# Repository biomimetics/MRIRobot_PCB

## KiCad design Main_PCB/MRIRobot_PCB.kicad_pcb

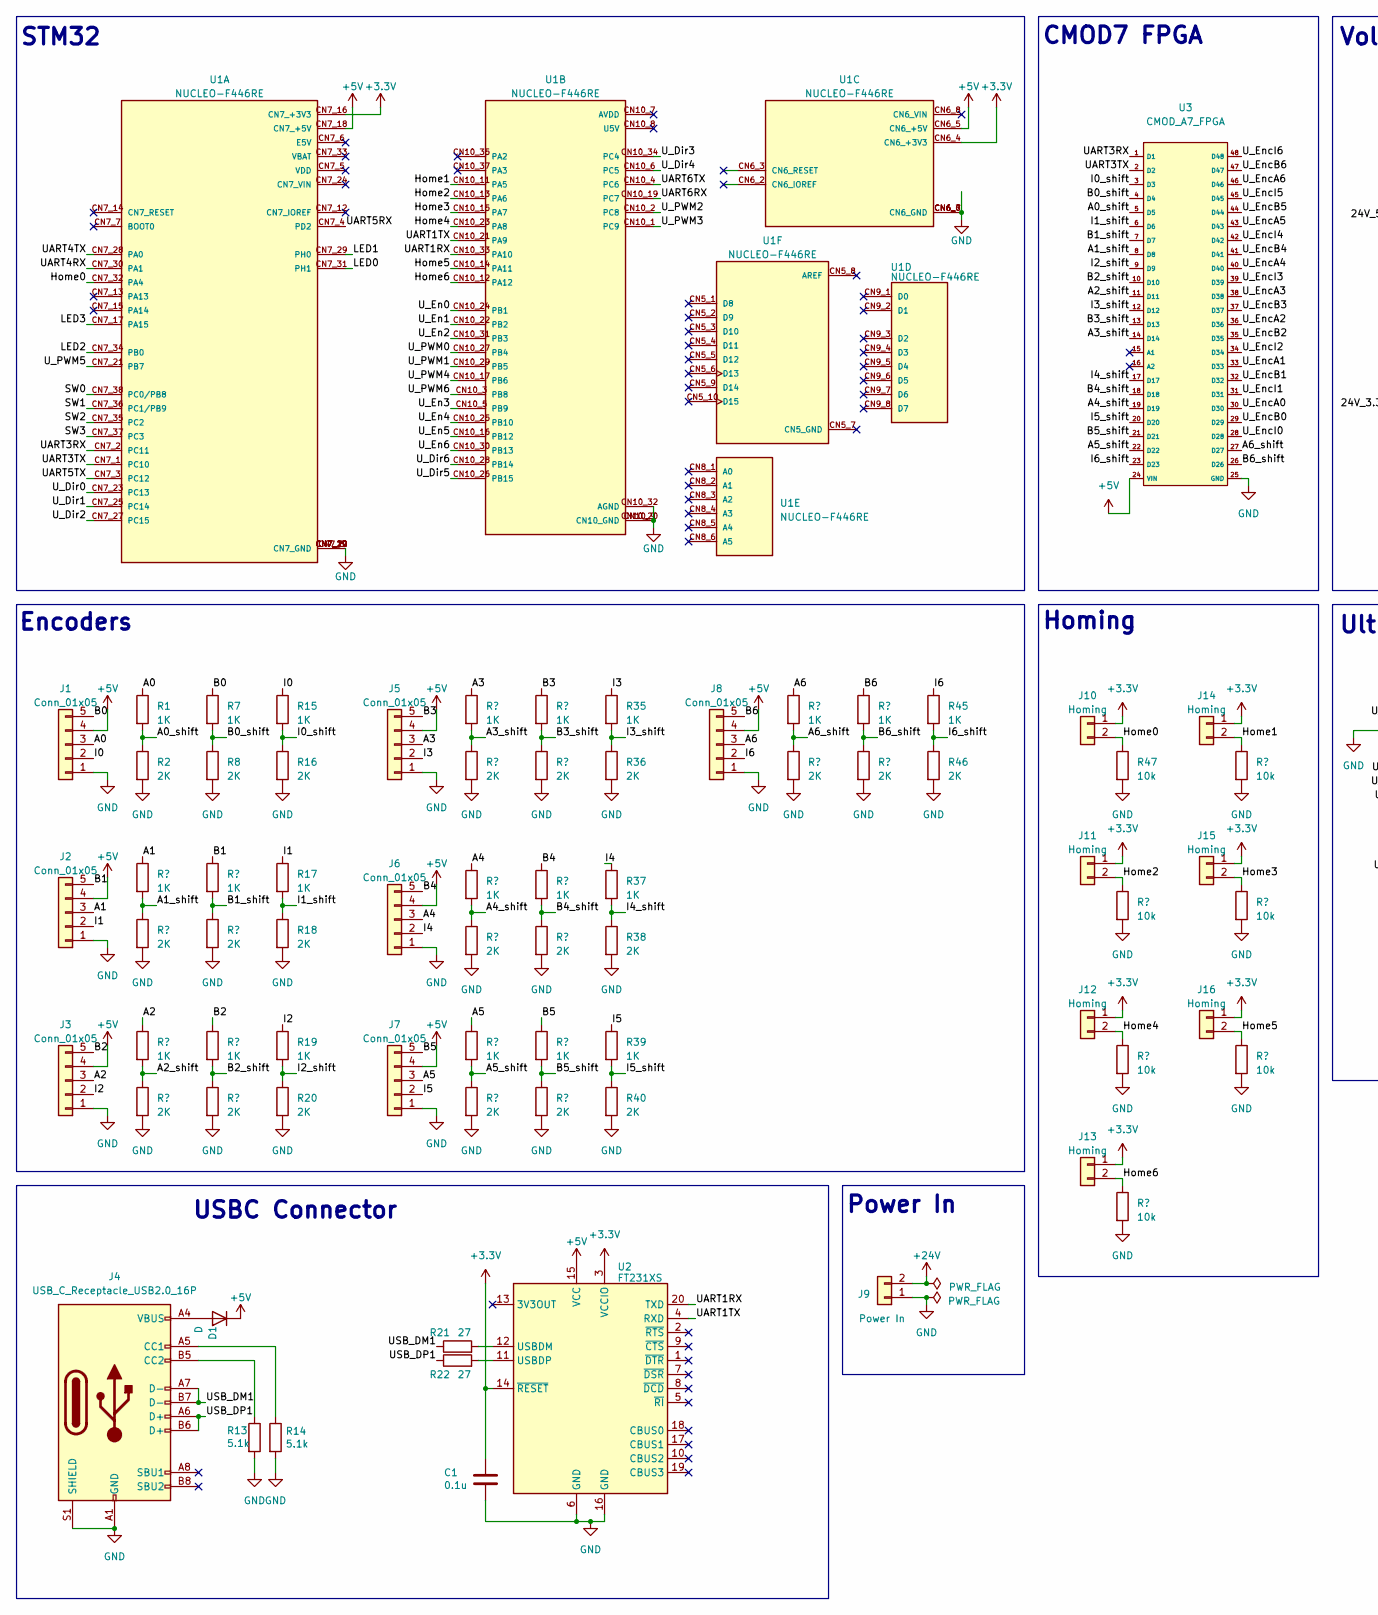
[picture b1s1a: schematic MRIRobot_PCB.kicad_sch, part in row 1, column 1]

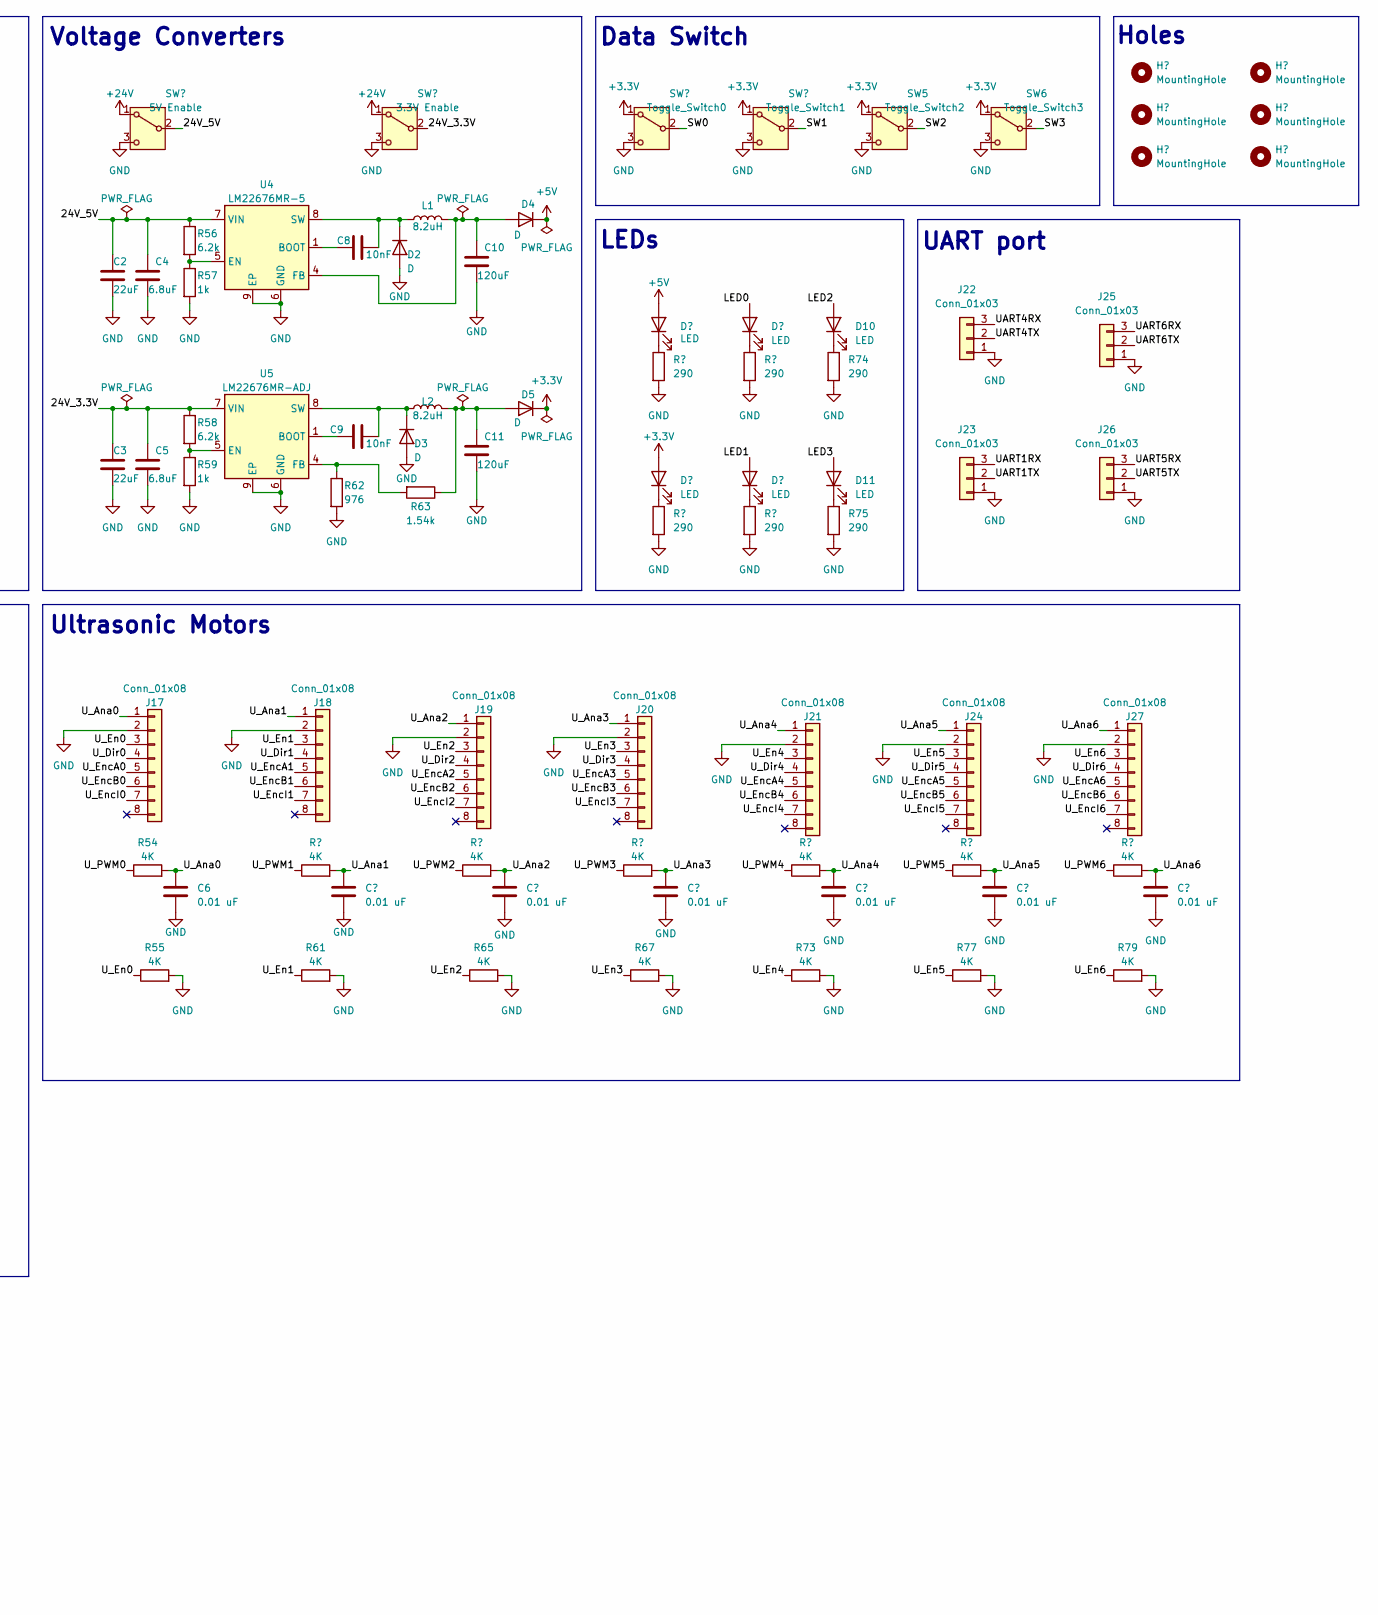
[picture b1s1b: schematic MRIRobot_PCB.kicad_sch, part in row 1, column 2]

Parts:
C1: 0.1u; C_0603_1608Metric_Pad1.08x0.95mm_HandSolder
C2, C3: 22uF; CP_Radial_D5.0mm_P2.00mm
C4, C5: 6.8uF; C_0805_2012Metric
C6, C7, C12, C13, C14, C15, C16: 0.01 uF; C_0805_2012Metric_Pad1.18x1.45mm_HandSolder
C8, C9: 10nF; C_0805_2012Metric
C10, C11: 120uF; CP_Radial_D6.3mm_P2.50mm
D1, D2, D3, D4, D5: D; D_SMA_Handsoldering
D6, D7, D8, D9, D10, D11: LED; LED_0805_2012Metric_Pad1.15x1.40mm_HandSolder
H1, H2, H3, H4, H5, H6: MountingHole; MountingHole_3.2mm_M3
J1, J2, J3, J5, J6, J7, J8: Conn_01x05; JST_EH_B5B-EH-A_1x05_P2.50mm_Vertical
J4: USB_C_Receptacle_USB2.0_16P; USB_C_Receptacle_GCT_USB4105-xx-A_16P_TopMnt_Horizontal
J9: Power In; AMASS_XT60-M_1x02_P7.20mm_Vertical
J10, J11, J12, J13, J14, J15, J16: Homing; JST_EH_B2B-EH-A_1x02_P2.50mm_Vertical
J17, J18, J19, J20, J21, J24, J27: Conn_01x08; JST_EH_B8B-EH-A_1x08_P2.50mm_Vertical
J22, J23, J25, J26: Conn_01x03; JST_XA_B03B-XASK-1-A_1x03_P2.50mm_Vertical
L1, L2: 8.2uH; L_7.3x7.3_H3.5
R1, R3, R5, R7, R9, R11, R15, R17, R19, R23, R25, R27, R29, R31, R33, R35, R37, R39, R41, R43, R45: 1K; C_0805_2012Metric_Pad1.18x1.45mm_HandSolder
R2, R4, R6, R8, R10, R12, R16, R18, R20, R24, R26, R28, R30, R32, R34, R36, R38, R40, R42, R44, R46: 2K; C_0805_2012Metric_Pad1.18x1.45mm_HandSolder
R13, R14: 5.1k; R_0603_1608Metric_Pad0.98x0.95mm_HandSolder
R21, R22: 27; R_0603_1608Metric_Pad0.98x0.95mm_HandSolder
R47, R48, R49, R50, R51, R52, R53: 10k; C_0805_2012Metric_Pad1.18x1.45mm_HandSolder
R54, R55, R60, R61, R64, R65, R66, R67, R72, R73, R76, R77, R78, R79: 4K; C_0805_2012Metric_Pad1.18x1.45mm_HandSolder
R56, R58: 6.2k; R_0805_2012Metric
R57, R59: 1k; R_0805_2012Metric
R62: 976; R_0805_2012Metric
R63: 1.54k; R_0805_2012Metric
R68, R69, R70, R71, R74, R75: 290; C_0805_2012Metric_Pad1.18x1.45mm_HandSolder
SW1: 5V Enable; SW_Slide_SPDT_Straight_CK_OS102011MS2Q
SW2: 3.3V Enable; SW_Slide_SPDT_Straight_CK_OS102011MS2Q
SW3: Toggle_Switch0; SW_Slide_SPDT_Straight_CK_OS102011MS2Q
SW4: Toggle_Switch1; SW_Slide_SPDT_Straight_CK_OS102011MS2Q
SW5: Toggle_Switch2; SW_Slide_SPDT_Straight_CK_OS102011MS2Q
SW6: Toggle_Switch3; SW_Slide_SPDT_Straight_CK_OS102011MS2Q
U1: NUCLEO-F446RE; MODULE_NUCLEO-F446RE; PARTREV 13
U2: FT231XS; SSOP-20_3.9x8.7mm_P0.635mm
U3: CMOD_A7_FPGA; CMODA7
U4: LM22676MR-5; TI_SO-PowerPAD-8
U5: LM22676MR-ADJ; TI_SO-PowerPAD-8

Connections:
+3.3V: C1.1, D5.1 (K), D7.2 (A), J10.1, J11.1, J12.1, J13.1, J14.1, J15.1, J16.1, SW3.1 (A), SW4.1 (A), SW5.1 (A), SW6.1 (A), U1.CN6_4 (CN6_+3V3), U1.CN7_16 (CN7_+3V3), U2.3 (VCCIO), U2.14 (~RESET)
+5V: D1.1 (K), D4.1 (K), D6.2 (A), J1.4, J2.4, J3.4, J5.4, J6.4, J7.4, J8.4, U1.CN6_5 (CN6_+5V), U1.CN7_18 (CN7_+5V), U2.15 (VCC), U3.24 (VIN)
+24V: J9.2, SW1.1 (A), SW2.1 (A)
/24V_3.3V: C3.1, C5.1, R58.1, SW2.2 (B), U5.7 (VIN)
/24V_5V: C2.1, C4.1, R56.1, SW1.2 (B), U4.7 (VIN)
/A0: J1.3, R1.1
/A0_shift: R1.2, R2.1, U3.5 (D5)
/A1: J2.3, R3.1
/A1_shift: R3.2, R4.1, U3.8 (D8)
/A2: J3.3, R5.1
/A2_shift: R5.2, R6.1, U3.11 (D11)
/A3: J5.3, R23.1
/A3_shift: R23.2, R24.1, U3.14 (D14)
/A4: J6.3, R25.1
/A4_shift: R25.2, R26.1, U3.19 (D19)
/A5: J7.3, R27.1
/A5_shift: R27.2, R28.1, U3.22 (D22)
/A6: J8.3, R41.1
/A6_shift: R41.2, R42.1, U3.27 (D27)
/B0: J1.5, R7.1
/B0_shift: R7.2, R8.1, U3.4 (D4)
/B1: J2.5, R9.1
/B1_shift: R9.2, R10.1, U3.7 (D7)
/B2: J3.5, R11.1
/B2_shift: R11.2, R12.1, U3.10 (D10)
/B3: J5.5, R29.1
/B3_shift: R29.2, R30.1, U3.13 (D13)
/B4: J6.5, R31.1
/B4_shift: R31.2, R32.1, U3.18 (D18)
/B5: J7.5, R33.1
/B5_shift: R33.2, R34.1, U3.21 (D21)
/B6: J8.5, R43.1
/B6_shift: R43.2, R44.1, U3.26 (D26)
/Home0: J10.2, R47.1, U1.CN7_32 (PA4)
/Home1: J14.2, R51.1, U1.CN10_11 (PA5)
/Home2: J11.2, R48.1, U1.CN10_13 (PA6)
/Home3: J15.2, R52.1, U1.CN10_15 (PA7)
/Home4: J12.2, R49.1, U1.CN10_23 (PA8)
/Home5: J16.2, R53.1, U1.CN10_14 (PA11)
/Home6: J13.2, R50.1, U1.CN10_12 (PA12)
/I0: J1.2, R15.1
/I0_shift: R15.2, R16.1, U3.3 (D3)
/I1: J2.2, R17.1
/I1_shift: R17.2, R18.1, U3.6 (D6)
/I2: J3.2, R19.1
/I2_shift: R19.2, R20.1, U3.9 (D9)
/I3: J5.2, R35.1
/I3_shift: R35.2, R36.1, U3.12 (D12)
/I4: J6.2, R37.1
/I4_shift: R37.2, R38.1, U3.17 (D17)
/I5: J7.2, R39.1
/I5_shift: R39.2, R40.1, U3.20 (D20)
/I6: J8.2, R45.1
/I6_shift: R45.2, R46.1, U3.23 (D23)
/LED0: D8.2 (A), U1.CN7_31 (PH1)
/LED1: D9.2 (A), U1.CN7_29 (PH0)
/LED2: D10.2 (A), U1.CN7_34 (PB0)
/LED3: D11.2 (A), U1.CN7_17 (PA15)
/SW0: SW3.2 (B), U1.CN7_38 (PC0/PB8)
/SW1: SW4.2 (B), U1.CN7_36 (PC1/PB9)
/SW2: SW5.2 (B), U1.CN7_35 (PC2)
/SW3: SW6.2 (B), U1.CN7_37 (PC3)
/UART1RX: J23.3, U1.CN10_33 (PA10), U2.20 (TXD)
/UART1TX: J23.2, U1.CN10_21 (PA9), U2.4 (RXD)
/UART3RX: U1.CN7_2 (PC11), U3.1 (D1)
/UART3TX: U1.CN7_1 (PC10), U3.2 (D2)
/UART4RX: J22.3, U1.CN7_30 (PA1)
/UART4TX: J22.2, U1.CN7_28 (PA0)
/UART5RX: J26.3, U1.CN7_4 (PD2)
/UART5TX: J26.2, U1.CN7_3 (PC12)
/UART6RX: J25.3, U1.CN10_19 (PC7)
/UART6TX: J25.2, U1.CN10_4 (PC6)
/USB_DM1: J4.A7 (D-), J4.B7 (D-), R21.1
/USB_DP1: J4.A6 (D+), J4.B6 (D+), R22.1
/U_Ana0: C6.1, J17.1, R54.2
/U_Ana1: C7.1, J18.1, R60.2
/U_Ana2: C12.1, J19.1, R64.2
/U_Ana3: C13.1, J20.1, R66.2
/U_Ana4: C14.1, J21.1, R72.2
/U_Ana5: C15.1, J24.1, R76.2
/U_Ana6: C16.1, J27.1, R78.2
/U_Dir0: J17.4, U1.CN7_23 (PC13)
/U_Dir1: J18.4, U1.CN7_25 (PC14)
/U_Dir2: J19.4, U1.CN7_27 (PC15)
/U_Dir3: J20.4, U1.CN10_34 (PC4)
/U_Dir4: J21.4, U1.CN10_6 (PC5)
/U_Dir5: J24.4, U1.CN10_26 (PB15)
/U_Dir6: J27.4, U1.CN10_28 (PB14)
/U_En0: J17.3, R55.1, U1.CN10_24 (PB1)
/U_En1: J18.3, R61.1, U1.CN10_22 (PB2)
/U_En2: J19.3, R65.1, U1.CN10_31 (PB3)
/U_En3: J20.3, R67.1, U1.CN10_5 (PB9)
/U_En4: J21.3, R73.1, U1.CN10_25 (PB10)
/U_En5: J24.3, R77.1, U1.CN10_16 (PB12)
/U_En6: J27.3, R79.1, U1.CN10_30 (PB13)
/U_EncA0: J17.5, U3.30 (D30)
/U_EncA1: J18.5, U3.33 (D33)
/U_EncA2: J19.5, U3.36 (D36)
/U_EncA3: J20.5, U3.38 (D38)
/U_EncA4: J21.5, U3.40 (D40)
/U_EncA5: J24.5, U3.43 (D43)
/U_EncA6: J27.5, U3.46 (D46)
/U_EncB0: J17.6, U3.29 (D29)
/U_EncB1: J18.6, U3.32 (D32)
/U_EncB2: J19.6, U3.35 (D35)
/U_EncB3: J20.6, U3.37 (D37)
/U_EncB4: J21.6, U3.41 (D41)
/U_EncB5: J24.6, U3.44 (D44)
/U_EncB6: J27.6, U3.47 (D47)
/U_EncI0: J17.7, U3.28 (D28)
/U_EncI1: J18.7, U3.31 (D31)
/U_EncI2: J19.7, U3.34 (D34)
/U_EncI3: J20.7, U3.39 (D39)
/U_EncI4: J21.7, U3.42 (D42)
/U_EncI5: J24.7, U3.45 (D45)
/U_EncI6: J27.7, U3.48 (D48)
/U_PWM0: R54.1, U1.CN10_27 (PB4)
/U_PWM1: R60.1, U1.CN10_29 (PB5)
/U_PWM2: R64.1, U1.CN10_2 (PC8)
/U_PWM3: R66.1, U1.CN10_1 (PC9)
/U_PWM4: R72.1, U1.CN10_17 (PB6)
/U_PWM5: R76.1, U1.CN7_21 (PB7)
/U_PWM6: R78.1, U1.CN10_3 (PB8)
GND: C1.2, C2.2, C3.2, C4.2, C5.2, C6.2, C7.2, C10.2, C11.2, C12.2, C13.2, C14.2, C15.2, C16.2, D2.2 (A), D3.2 (A), J1.1, J2.1, J3.1, J4.A1 (GND), J4.A12 (GND), J4.B1 (GND), J4.B12 (GND), J4.S1 (SHIELD), J5.1, J6.1, J7.1, J8.1, J9.1, J17.2, J18.2, J19.2, J20.2, J21.2, J22.1, J23.1, J24.2, J25.1, J26.1, J27.2, R2.2, R4.2, R6.2, R8.2, R10.2, R12.2, R13.2, R14.2, R16.2, R18.2, R20.2, R24.2, R26.2, R28.2, R30.2, R32.2, R34.2, R36.2, R38.2, R40.2, R42.2, R44.2, R46.2, R47.2, R48.2, R49.2, R50.2, R51.2, R52.2, R53.2, R55.2, R57.2, R59.2, R61.2, R62.2, R65.2, R67.2, R68.2, R69.2, R70.2, R71.2, R73.2, R74.2, R75.2, R77.2, R79.2, SW1.3 (C), SW2.3 (C), SW3.3 (C), SW4.3 (C), SW5.3 (C), SW6.3 (C), U1.CN6_6 (CN6_GND), U1.CN6_7 (CN6_GND), U1.CN7_8 (CN7_GND), U1.CN7_19 (CN7_GND), U1.CN7_20 (CN7_GND), U1.CN7_22 (CN7_GND), U1.CN10_9 (CN10_GND), U1.CN10_20 (CN10_GND), U1.CN10_32 (AGND), U2.6 (GND), U2.16 (GND), U3.25 (GND), U4.6 (GND), U4.9 (EP), U5.6 (GND), U5.9 (EP)
unnamed: D1.2 (A), J4.A4 (VBUS), J4.A9 (VBUS), J4.B4 (VBUS), J4.B9 (VBUS)
unnamed: C8.2, D2.1 (K), L1.1, U4.8 (SW)
unnamed: C9.2, D3.1 (K), L2.1, U5.8 (SW)
unnamed: C10.1, D4.2 (A), L1.2, U4.4 (FB)
unnamed: C11.1, D5.2 (A), L2.2, R63.1
unnamed: D6.1 (K), R68.1
unnamed: D7.1 (K), R69.1
unnamed: D8.1 (K), R70.1
unnamed: D9.1 (K), R71.1
unnamed: D10.1 (K), R74.1
unnamed: D11.1 (K), R75.1
unnamed: J4.A5 (CC1), R14.1
unnamed: J4.B5 (CC2), R13.1
unnamed: R21.2, U2.12 (USBDM)
unnamed: R22.2, U2.11 (USBDP)
unnamed: C8.1, U4.1 (BOOT)
unnamed: R56.2, R57.1, U4.5 (EN)
unnamed: C9.1, U5.1 (BOOT)
unnamed: R58.2, R59.1, U5.5 (EN)
unnamed: R62.1, R63.2, U5.4 (FB)

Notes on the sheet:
Holes
STM32
LEDs
Data Switch
Ultrasonic Motors
Homing
USBC Connector
CMOD7 FPGA
Power In
UART port
Encoders
Voltage Converters

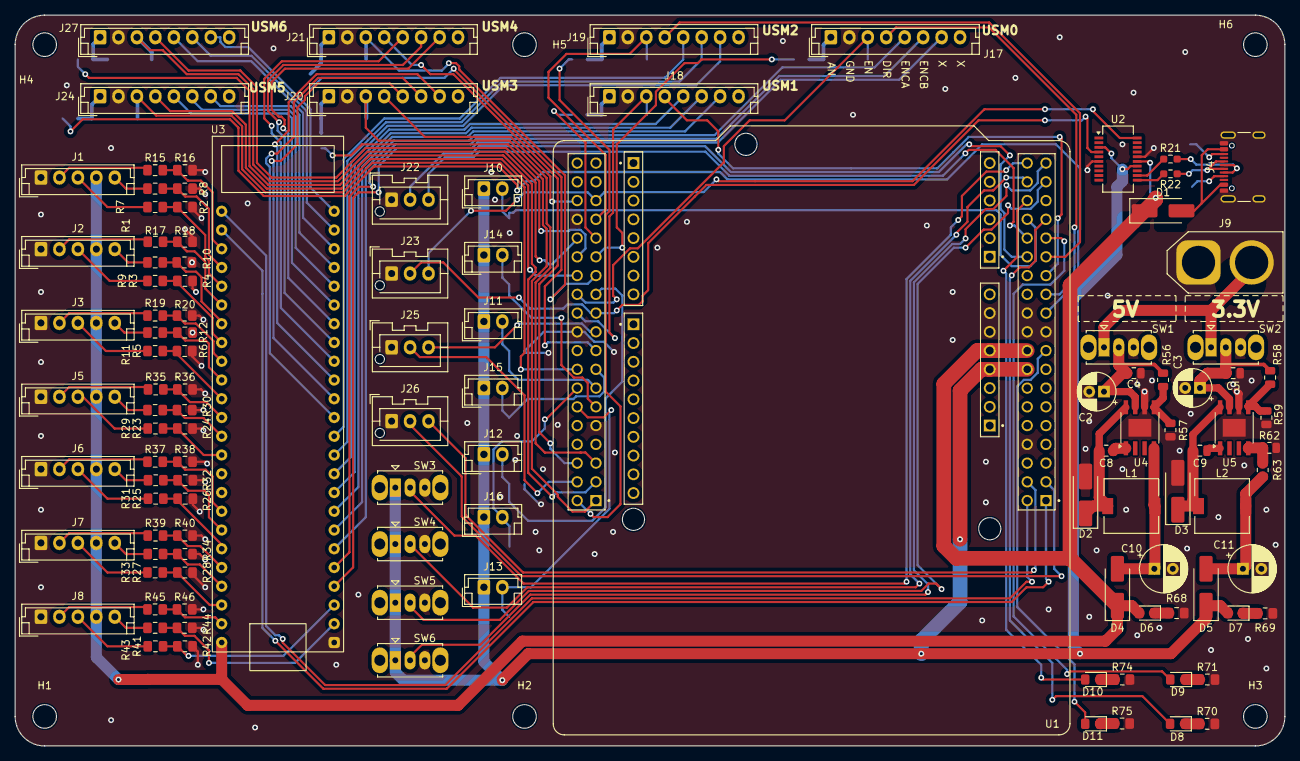
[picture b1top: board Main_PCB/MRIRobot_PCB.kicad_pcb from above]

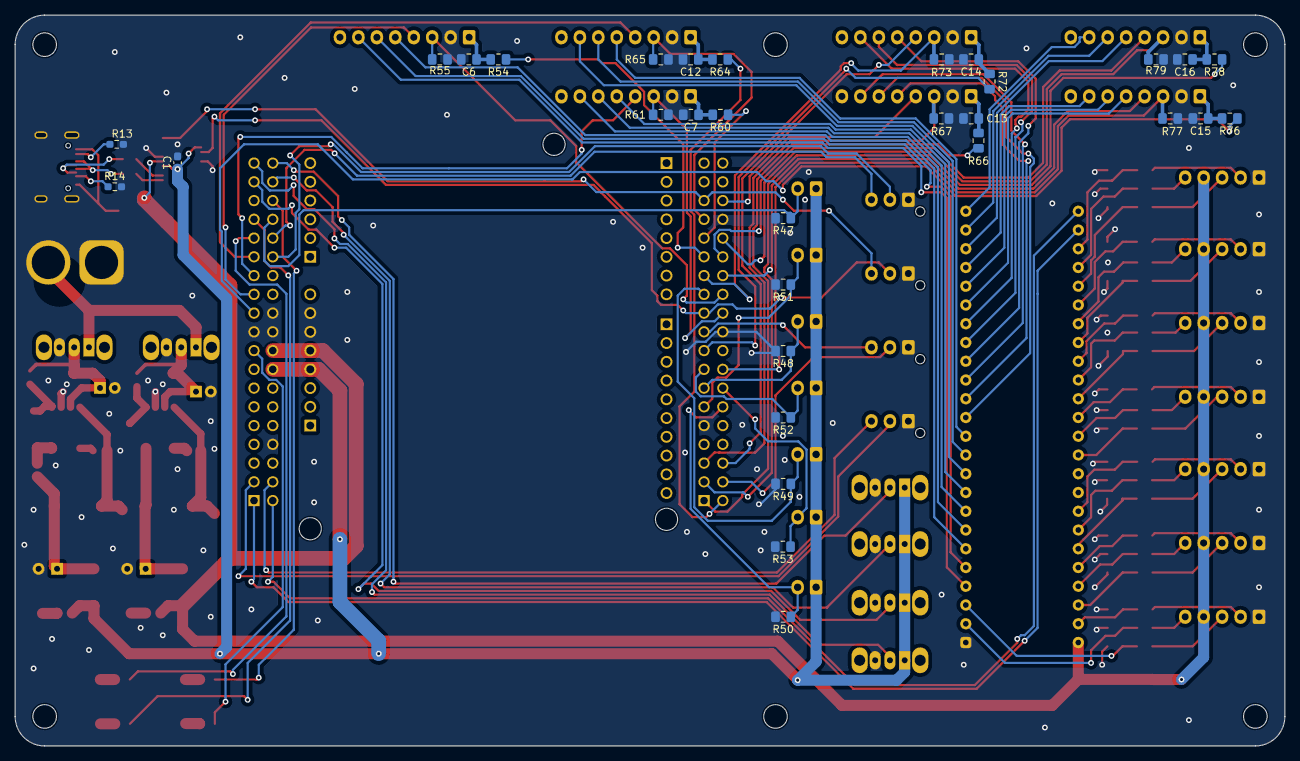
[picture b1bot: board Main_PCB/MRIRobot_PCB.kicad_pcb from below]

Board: 2 copper layers, 172.0 x 99.0 mm, 152 parts (31 on the bottom side), 144 nets.
